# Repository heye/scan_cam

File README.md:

# scan_cam

files for my scanning camera 

[https://hackaday.io/project/160425-digital-scanning-back-with-linear-ccd]

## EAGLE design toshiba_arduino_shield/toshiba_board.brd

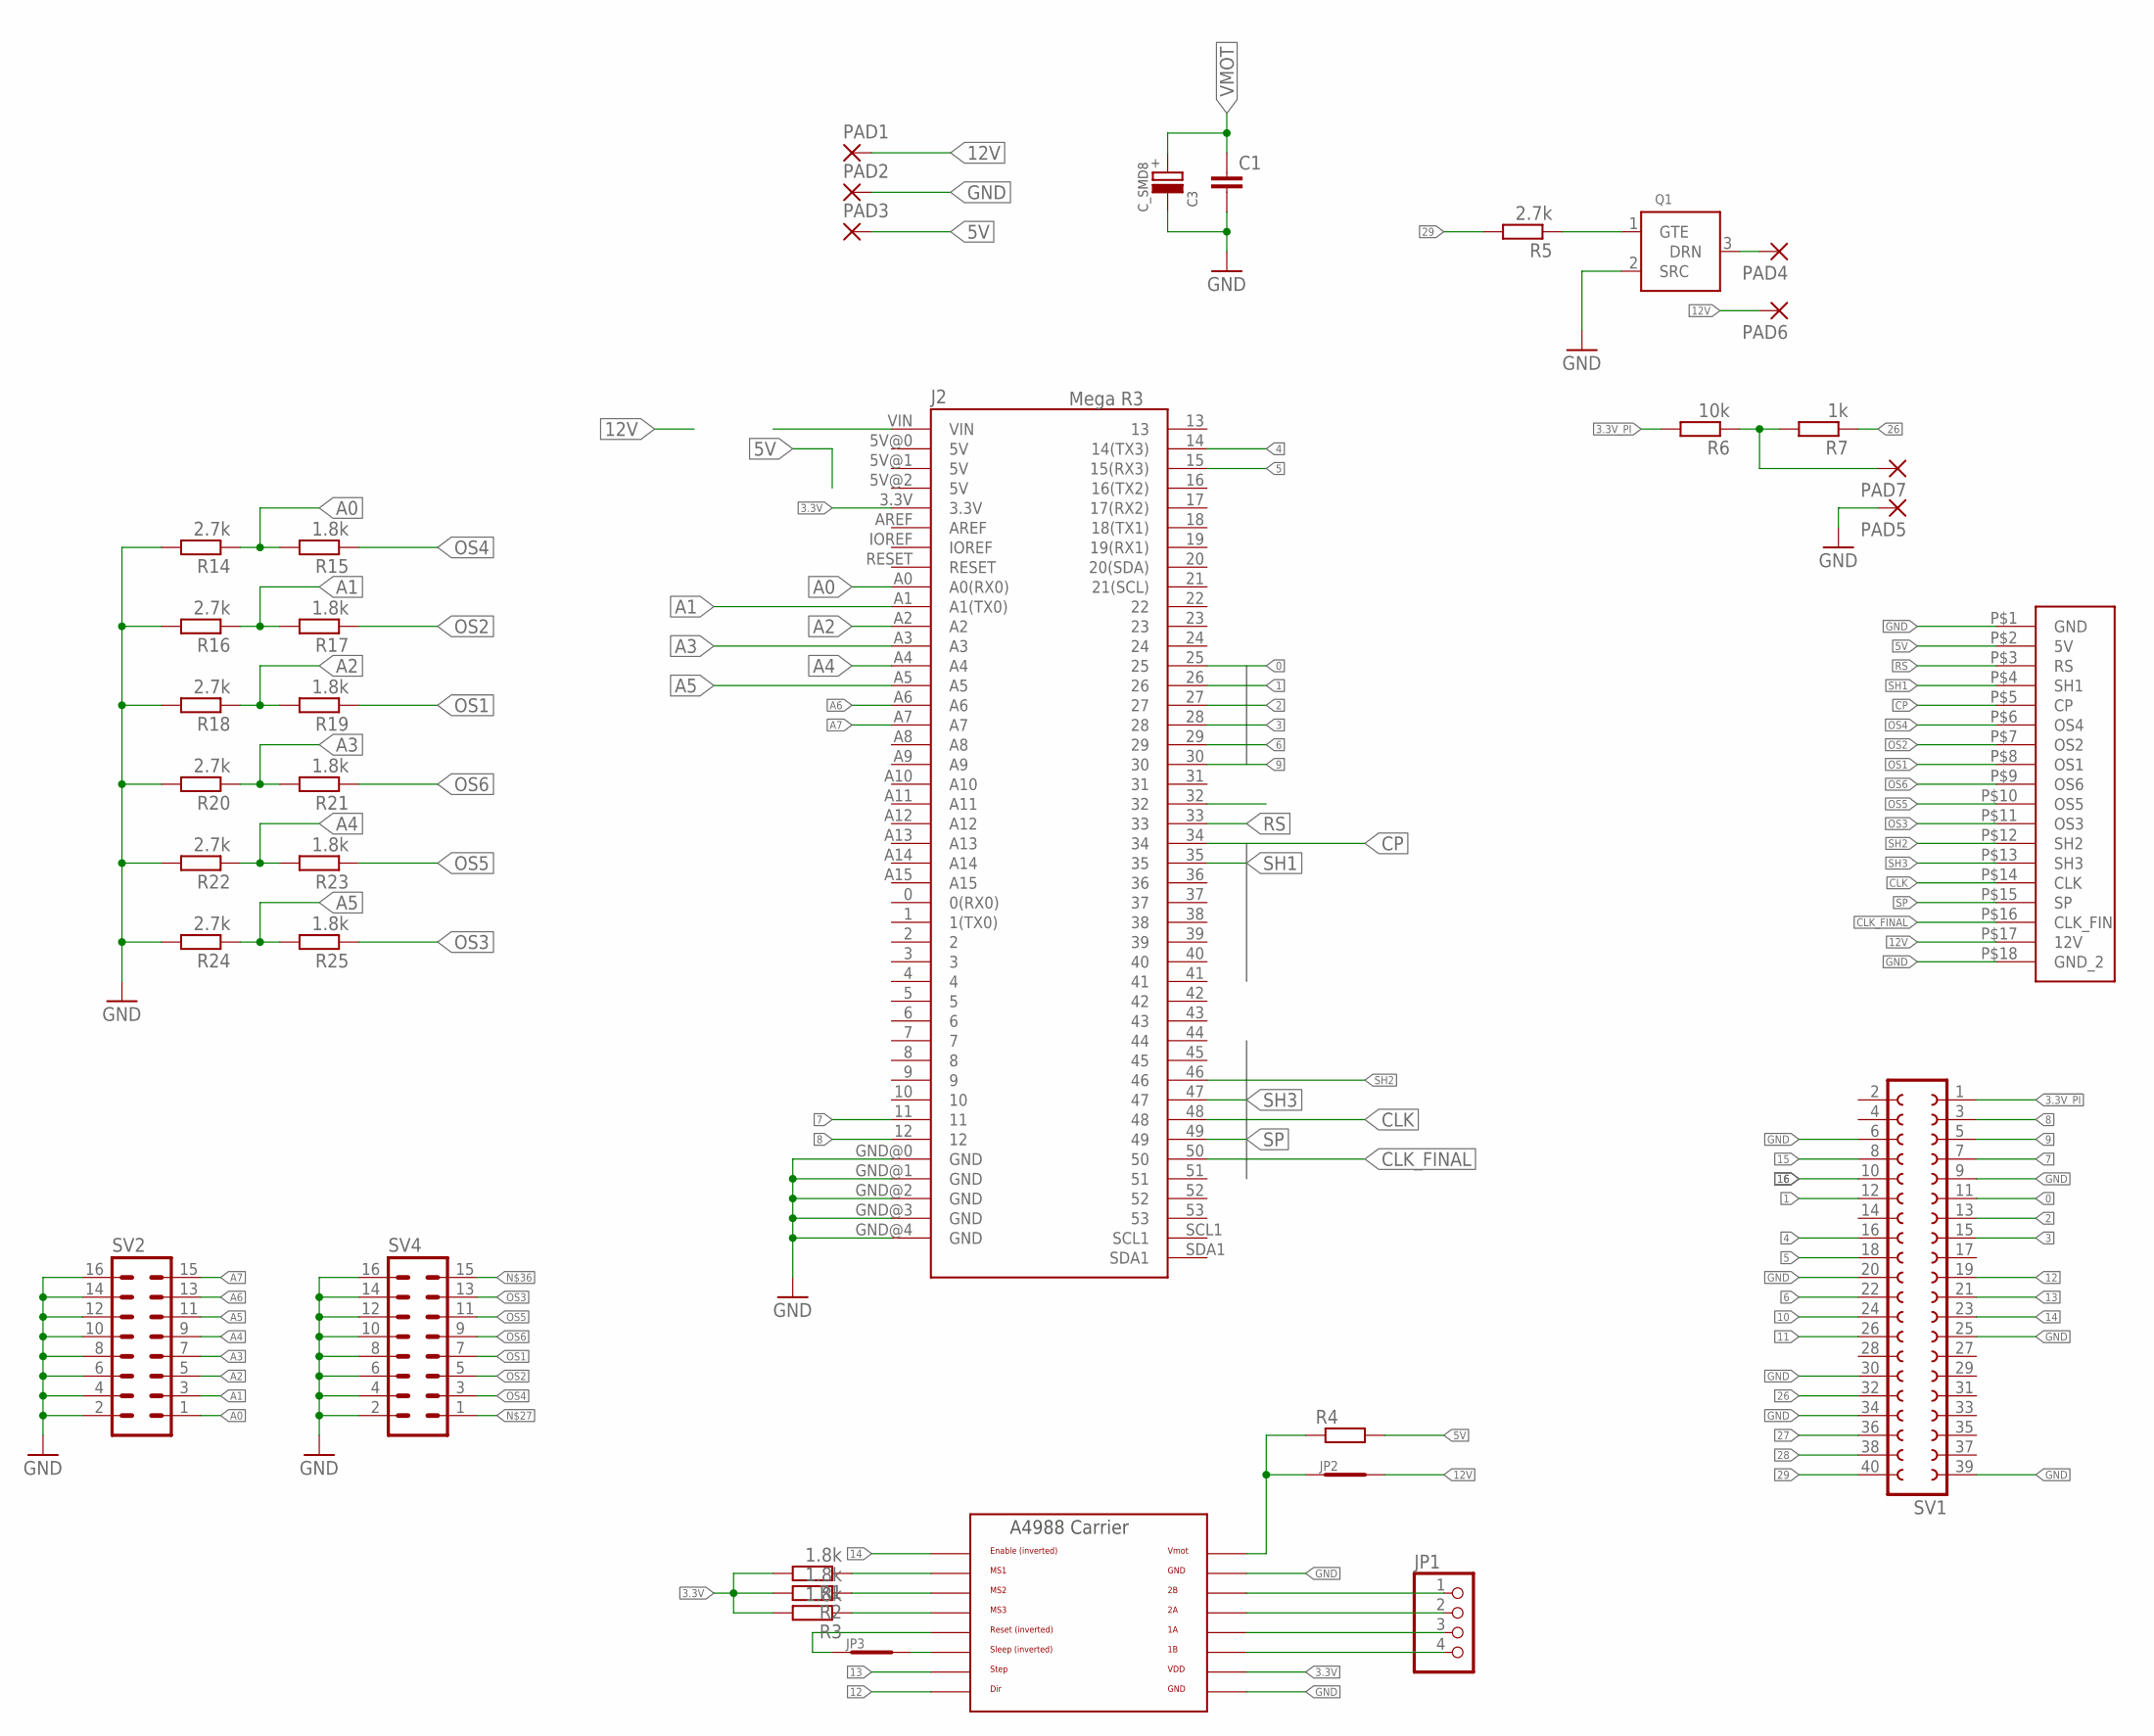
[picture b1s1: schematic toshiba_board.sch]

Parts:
C1: C-EUC0805; C0805
C3: C_SMD8; C-SMD-8MM
J2: Mega R3; ARDUINO_MEGA
JP1: PINHD-1X4; 1X04
JP2, JP3: SHORT0805; 0805_SHORT
PAD1, PAD2, PAD3, PAD4, PAD5, PAD6, PAD7: SMD2; SMD1,27-2,54
Q1: BSS138; SOT23
R1, R2, R3, R15, R17, R19, R21, R23, R25: 1.8k; R0603
R4: R-EU_R0805; R0805
R5, R14, R16, R18, R20, R22, R24: 2.7k; R0603
R6: 10k; R0603
R7: 1k; R0603
SV1: FE20-2
SV2, SV4: MA08-2
U$1: PIN_18; PAD_18
U$2: POLOLU_A4983CARRIER; A4988BREAKOUT

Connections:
0: J2.25, SV1.11
1: J2.26, SV1.12
2: J2.27, SV1.13
3: J2.28, SV1.15
3.3V: J2.3.3V, R1.2, R2.2, R3.2, U$2.VDD
3.3V_PI: R6.2, SV1.1
4: J2.14 (14(TX3)), SV1.16
5: J2.15 (15(RX3)), SV1.18
5V: PAD3.1, R4.2, U$1.P$2 (5V)
6: J2.29, SV1.22
7: J2.11, SV1.7
8: J2.12, SV1.3
9: J2.30, SV1.5
10: SV1.24
11: SV1.26
12: SV1.19, U$2.DIR
12V: JP2.P$2, PAD1.1, PAD6.1, U$1.P$17 (12V)
13: SV1.21, U$2.STEP
14: SV1.23, U$2.EN
15: SV1.8
16: SV1.10
26: R7.1, SV1.32
27: SV1.36
28: SV1.38
29: R5.2, SV1.40
A0: J2.A0 (A0(RX0)), R14.1, R15.2, SV2.1
A1: J2.A1 (A1(TX0)), R16.1, R17.2, SV2.3
A2: J2.A2, R18.1, R19.2, SV2.5
A3: J2.A3, R20.1, R21.2, SV2.7
A4: J2.A4, R22.1, R23.2, SV2.9
A5: J2.A5, R24.1, R25.2, SV2.11
A6: J2.A6, SV2.13
A7: J2.A7, SV2.15
CLK: J2.48, U$1.P$14 (CLK)
CLK_FINAL: J2.50, U$1.P$16 (CLK_FIN)
CP: J2.34, U$1.P$5 (CP)
GND: C1.2, C3.-, J2.GND@0 (GND), J2.GND@1 (GND), J2.GND@2 (GND), J2.GND@3 (GND), J2.GND@4 (GND), PAD2.1, PAD5.1, Q1.2 (SRC), R14.2, R16.2, R18.2, R20.2, R22.2, R24.2, SV1.6, SV1.9, SV1.20, SV1.25, SV1.30, SV1.34, SV1.39, SV2.2, SV2.4, SV2.6, SV2.8, SV2.10, SV2.12, SV2.14, SV2.16, SV4.2, SV4.4, SV4.6, SV4.8, SV4.10, SV4.12, SV4.14, SV4.16, U$1.P$1 (GND), U$1.P$18 (GND_2), U$2.GND, U$2.GND@0 (GND)
unnamed: Q1.1 (GTE), R5.1
unnamed: JP1.1, U$2.2B
unnamed: JP1.2, U$2.2A
unnamed: JP1.3, U$2.1A
unnamed: PAD7.1, R6.1, R7.2
unnamed: PAD4.1, Q1.3 (DRN)
unnamed: JP1.4, U$2.1B
unnamed: R1.1, U$2.MS1
unnamed: R2.1, U$2.MS2
unnamed: JP3.P$2, U$2.SLP (SLEEP)
unnamed: R3.1, U$2.MS3
unnamed: JP3.P$1, U$2.RST
OS1: R19.1, SV4.7, U$1.P$8 (OS1)
OS2: R17.1, SV4.5, U$1.P$7 (OS2)
OS3: R25.1, SV4.13, U$1.P$11 (OS3)
OS4: R15.1, SV4.3, U$1.P$6 (OS4)
OS5: R23.1, SV4.11, U$1.P$10 (OS5)
OS6: R21.1, SV4.9, U$1.P$9 (OS6)
RS: J2.33, U$1.P$3 (RS)
SH1: J2.35, U$1.P$4 (SH1)
SH2: J2.46, U$1.P$12 (SH2)
SH3: J2.47, U$1.P$13 (SH3)
SP: J2.49, U$1.P$15 (SP)
VMOT: C1.1, C3.+, JP2.P$1, R4.1, U$2.VMOT

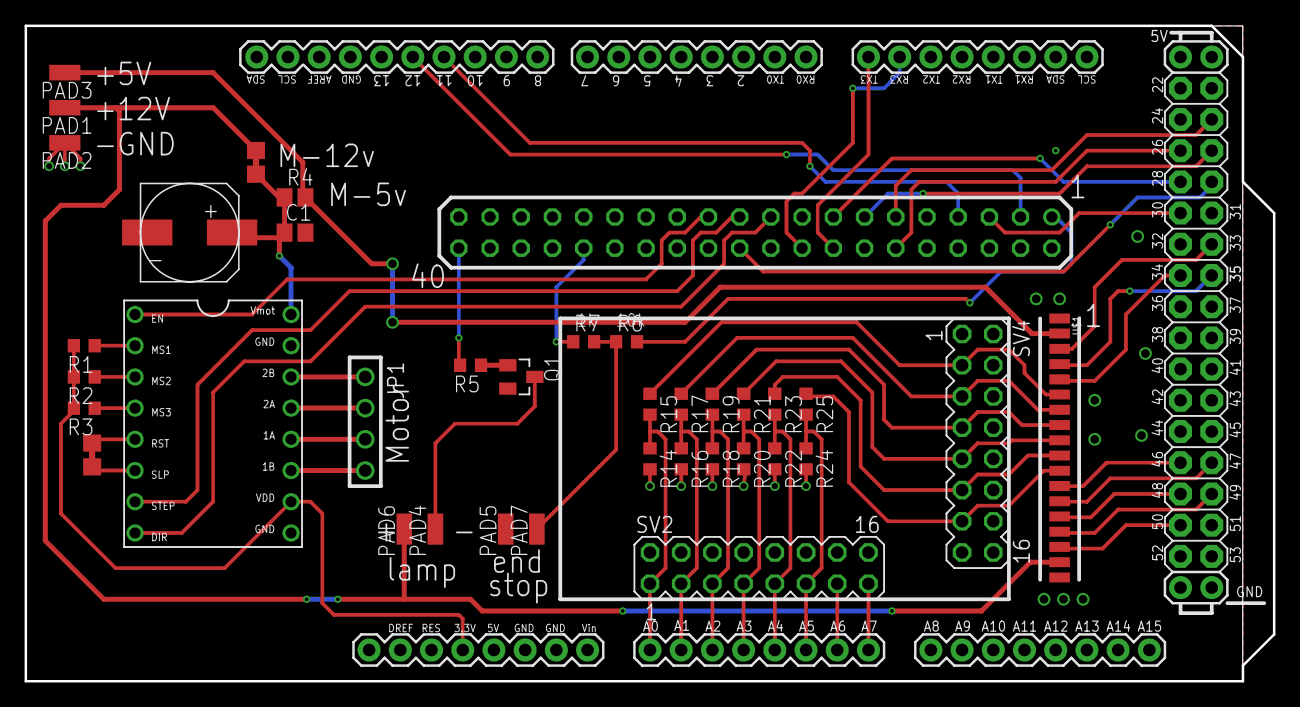
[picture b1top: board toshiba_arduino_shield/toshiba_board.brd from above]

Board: 2 copper layers, 101.6 x 53.3 mm, 38 parts (1 on the bottom side), 55 nets.

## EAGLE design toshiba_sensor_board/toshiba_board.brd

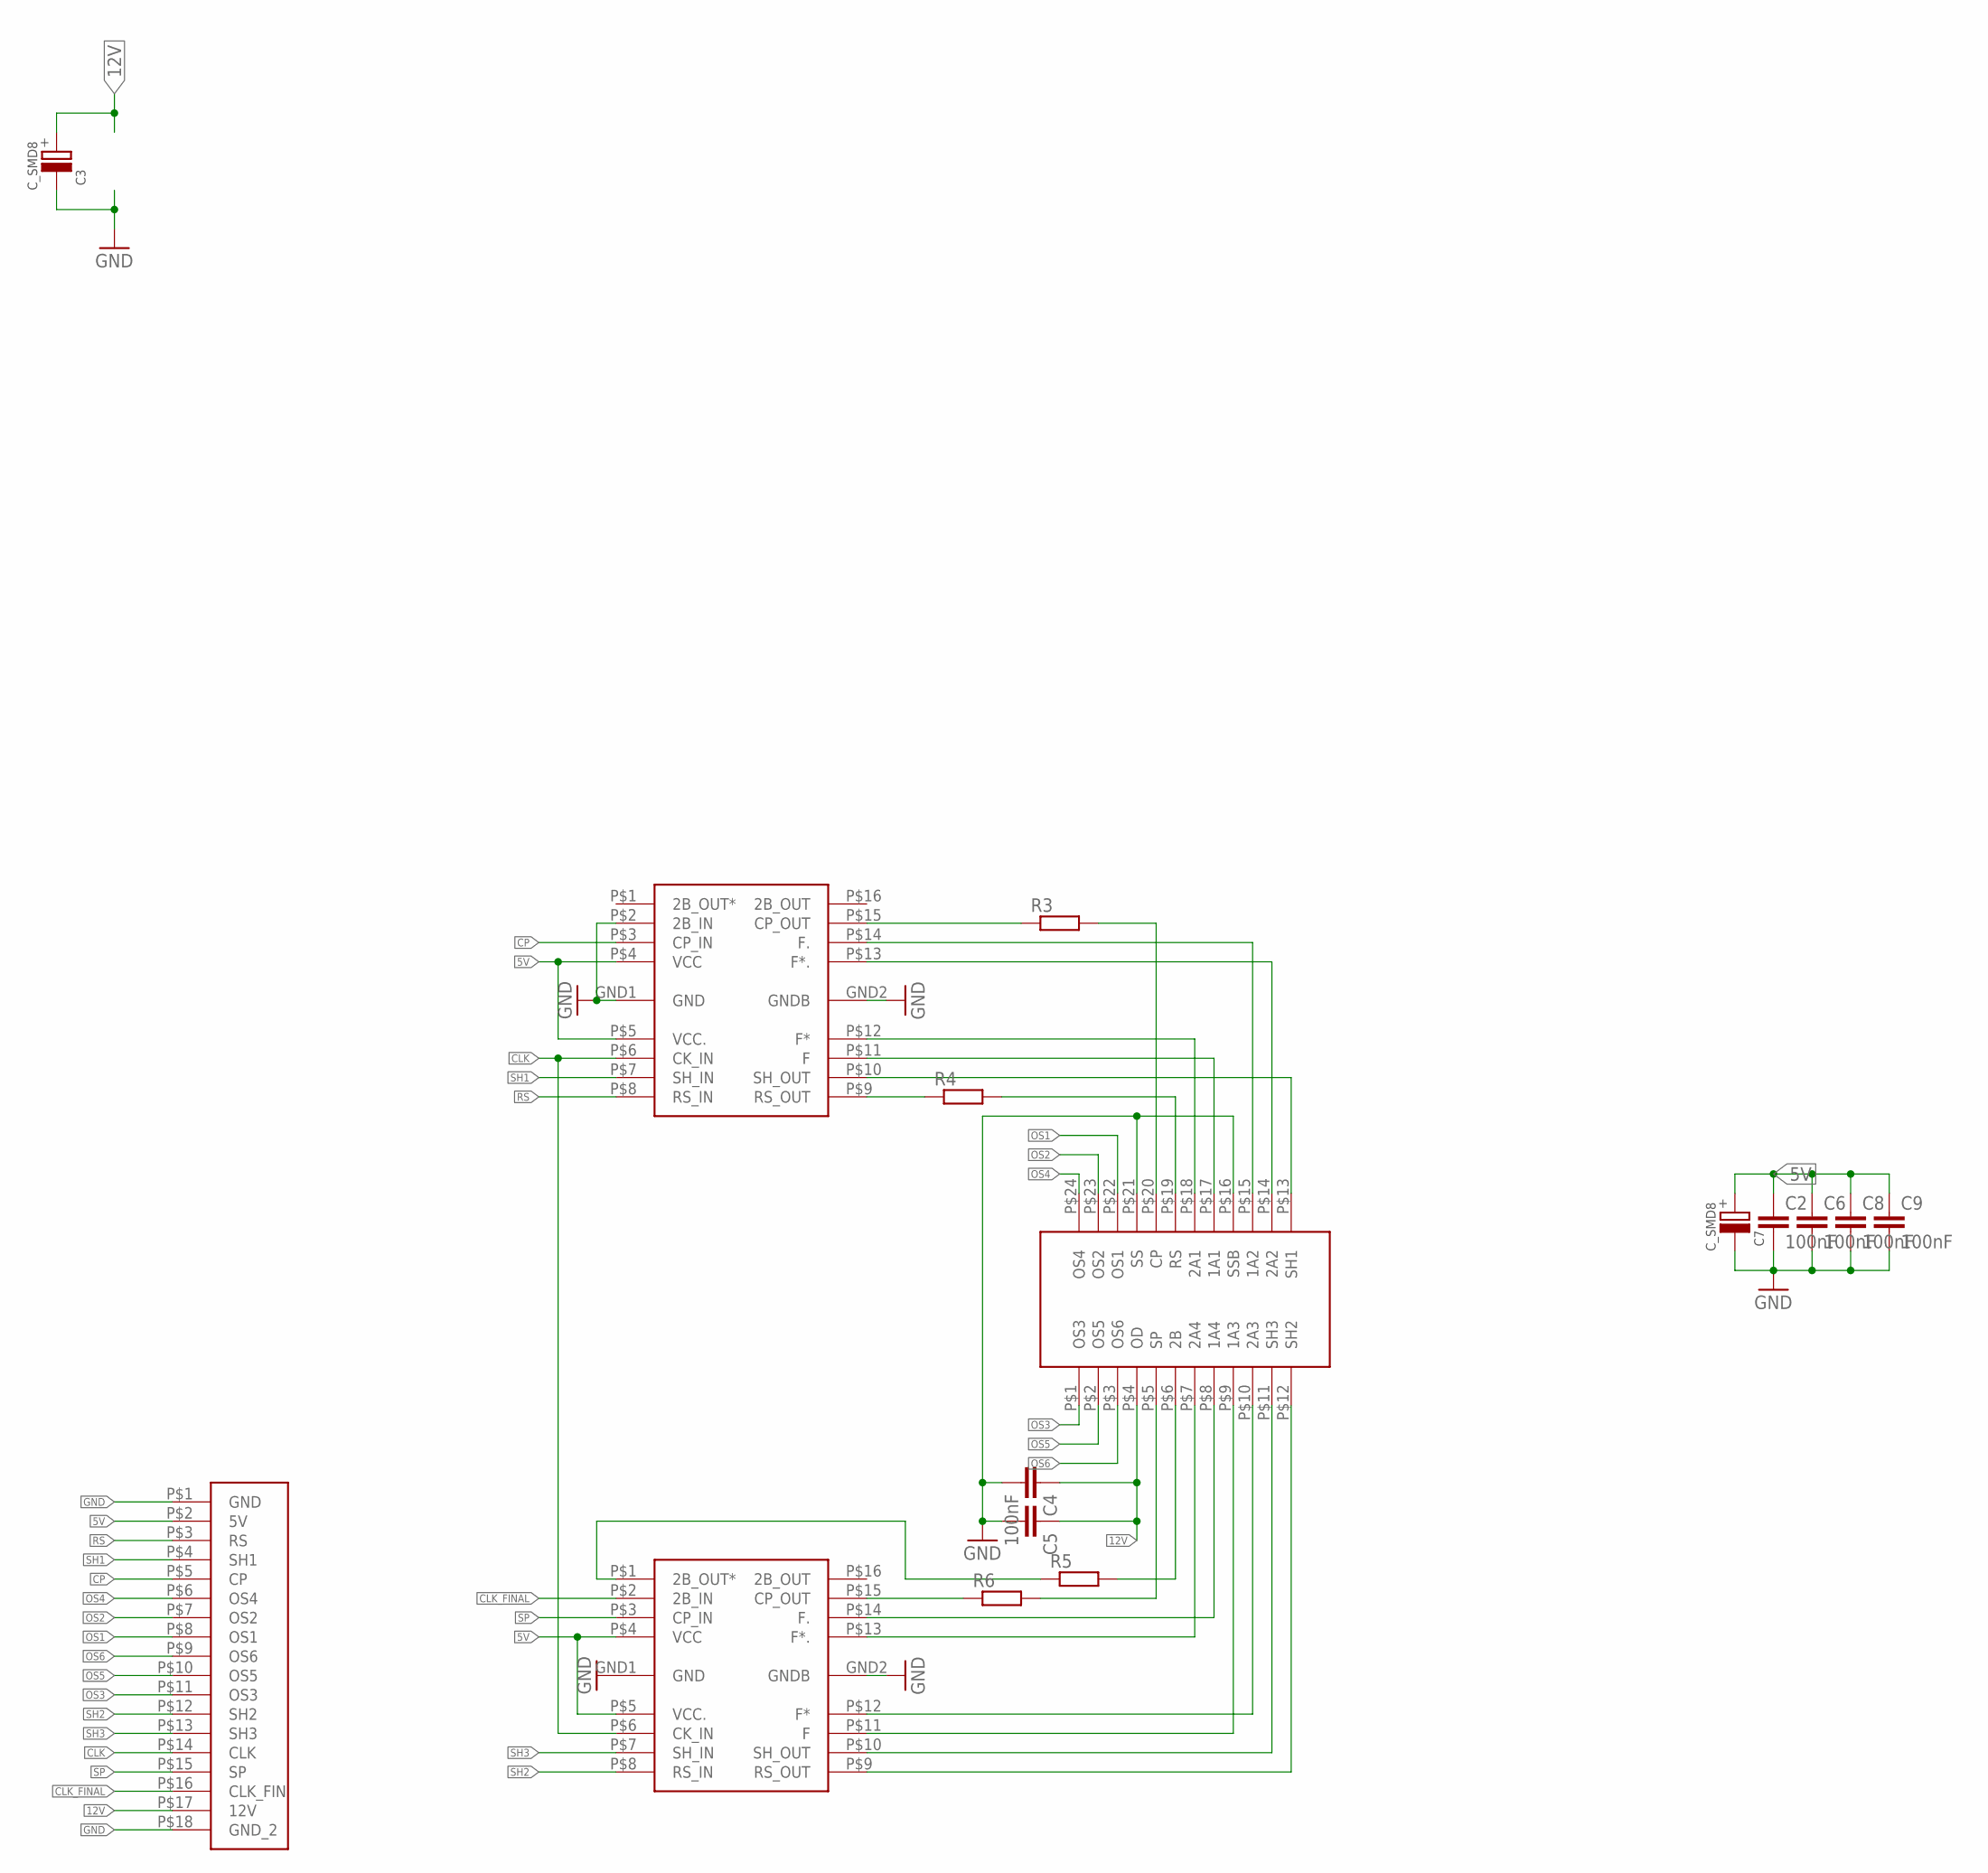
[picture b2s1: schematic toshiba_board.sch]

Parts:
C2, C4, C6, C8, C9: 100nF; C0603
C3, C7: C_SMD8; C-SMD-8MM
C5: C-EUC0805; C0805
R3, R4, R5, R6: R-EU_R0603; R0603
U$1, U$3: TB62801F
U$2: TCD2700TCD; TCD2700
U$4: PIN_18; PAD_18

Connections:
5V: C2.1, C6.1, C7.+, C8.1, C9.1, U$1.P$4 (VCC), U$1.P$5 (VCC.), U$3.P$4 (VCC), U$3.P$5 (VCC.), U$4.P$2 (5V)
12V: C3.+, C4.1, C5.1, U$2.P$4 (OD), U$4.P$17 (12V)
CLK: U$1.P$6 (CK_IN), U$3.P$6 (CK_IN), U$4.P$14 (CLK)
CLK_FINAL: U$1.P$2 (2B_IN), U$4.P$16 (CLK_FIN)
CP: U$3.P$3 (CP_IN), U$4.P$5 (CP)
GND: C2.2, C3.-, C4.2, C5.2, C6.2, C7.-, C8.2, C9.2, U$1.GND1 (GND), U$1.GND2 (GNDB), U$2.P$16 (SSB), U$2.P$21 (SS), U$3.GND1 (GND), U$3.GND2 (GNDB), U$3.P$2 (2B_IN), U$4.P$1 (GND), U$4.P$18 (GND_2)
unnamed: U$1.P$9 (RS_OUT), U$2.P$12 (SH2)
unnamed: U$1.P$10 (SH_OUT), U$2.P$11 (SH3)
unnamed: U$1.P$11 (F), U$2.P$9 (1A3)
unnamed: U$1.P$12 (F*), U$2.P$10 (2A3)
unnamed: U$1.P$13 (F*.), U$2.P$7 (2A4)
unnamed: U$1.P$14 (F.), U$2.P$8 (1A4)
unnamed: R6.1, U$1.P$15 (CP_OUT)
unnamed: R6.2, U$2.P$5 (SP)
unnamed: R5.1, U$1.P$1 (2B_OUT*)
unnamed: R5.2, U$2.P$6 (2B)
unnamed: R3.2, U$2.P$20 (CP)
unnamed: U$2.P$15 (1A2), U$3.P$14 (F.)
unnamed: U$2.P$14 (2A2), U$3.P$13 (F*.)
unnamed: U$2.P$18 (2A1), U$3.P$12 (F*)
unnamed: U$2.P$17 (1A1), U$3.P$11 (F)
unnamed: U$2.P$13 (SH1), U$3.P$10 (SH_OUT)
unnamed: R3.1, U$3.P$15 (CP_OUT)
unnamed: R4.2, U$2.P$19 (RS)
unnamed: R4.1, U$3.P$9 (RS_OUT)
OS1: U$2.P$22 (OS1), U$4.P$8 (OS1)
OS2: U$2.P$23 (OS2), U$4.P$7 (OS2)
OS3: U$2.P$1 (OS3), U$4.P$11 (OS3)
OS4: U$2.P$24 (OS4), U$4.P$6 (OS4)
OS5: U$2.P$2 (OS5), U$4.P$10 (OS5)
OS6: U$2.P$3 (OS6), U$4.P$9 (OS6)
RS: U$3.P$8 (RS_IN), U$4.P$3 (RS)
SH1: U$3.P$7 (SH_IN), U$4.P$4 (SH1)
SH2: U$1.P$8 (RS_IN), U$4.P$12 (SH2)
SH3: U$1.P$7 (SH_IN), U$4.P$13 (SH3)
SP: U$1.P$3 (CP_IN), U$4.P$15 (SP)

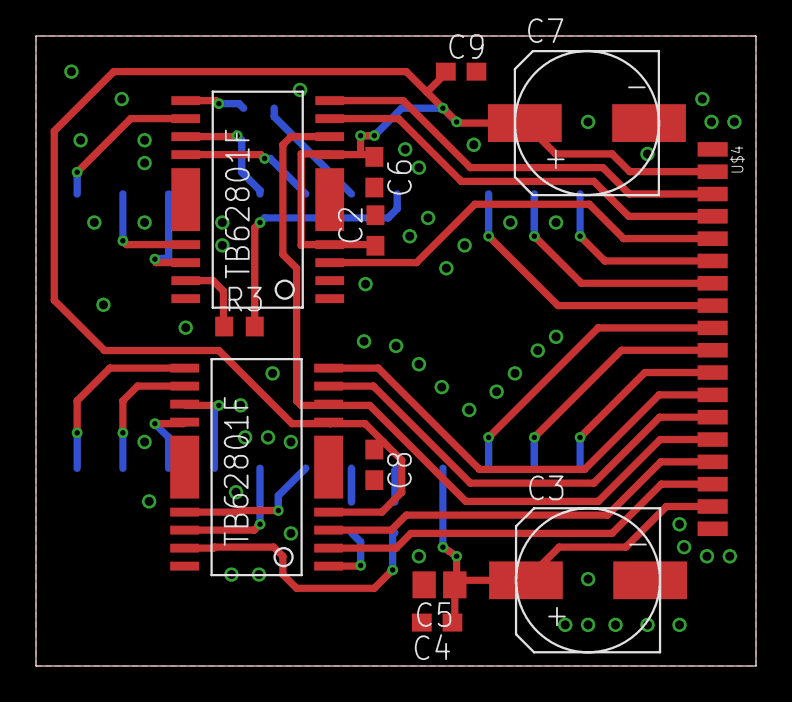
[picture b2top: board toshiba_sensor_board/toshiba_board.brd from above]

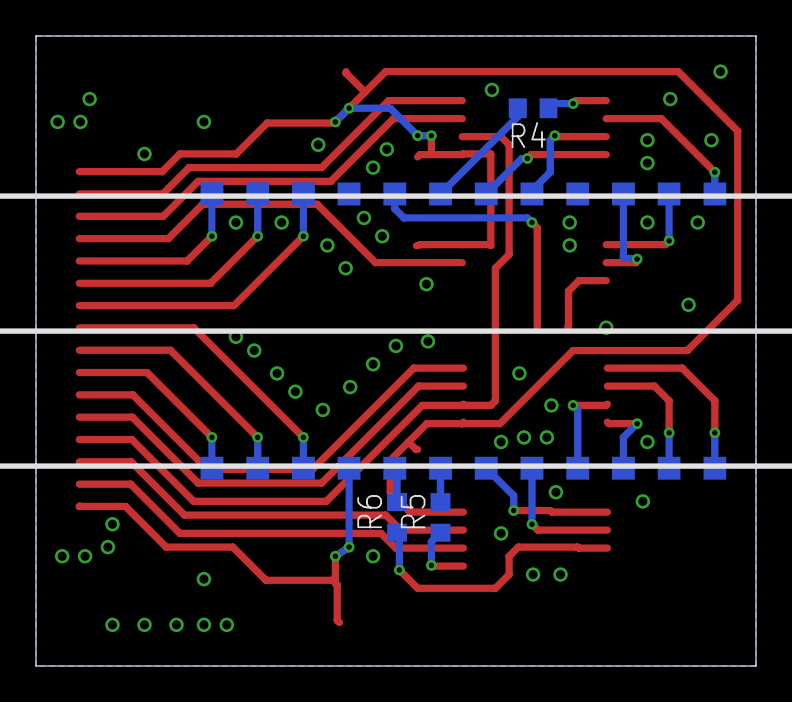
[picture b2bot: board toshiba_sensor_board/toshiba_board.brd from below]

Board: 2 copper layers, 40.0 x 35.0 mm, 16 parts (4 on the bottom side), 36 nets.

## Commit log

2018-08-14 add files
2018-09-23 add teensy arduino sketch and post processing python script
